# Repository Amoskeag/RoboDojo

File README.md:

# RoboDojo

This repo contains all the firmware and hardware for the RoboDojo.

If you're looking for the latest docs/builds, see our [Releases Page](https://github.com/Amoskeag/RoboDojo/releases).

# Getting Started

First, clone this repo (and optionally checkout a branch)

```shell
git clone --recurse-submodules https://github.com/Amoskeag/RoboDojo.git
cd RoboDojo
```

# Re-Init Submodules

Some libraries and resources are included as submodules, run the following
command to initialize them before opening the main sch

(If you get a missing library error, make sure to do this)

```shell
git submodule update --init --recursive
```

## Project Layout

If you want to use this project template for yourself, you can find it [here!](https://github.com/KenwoodFox/Project-Template)

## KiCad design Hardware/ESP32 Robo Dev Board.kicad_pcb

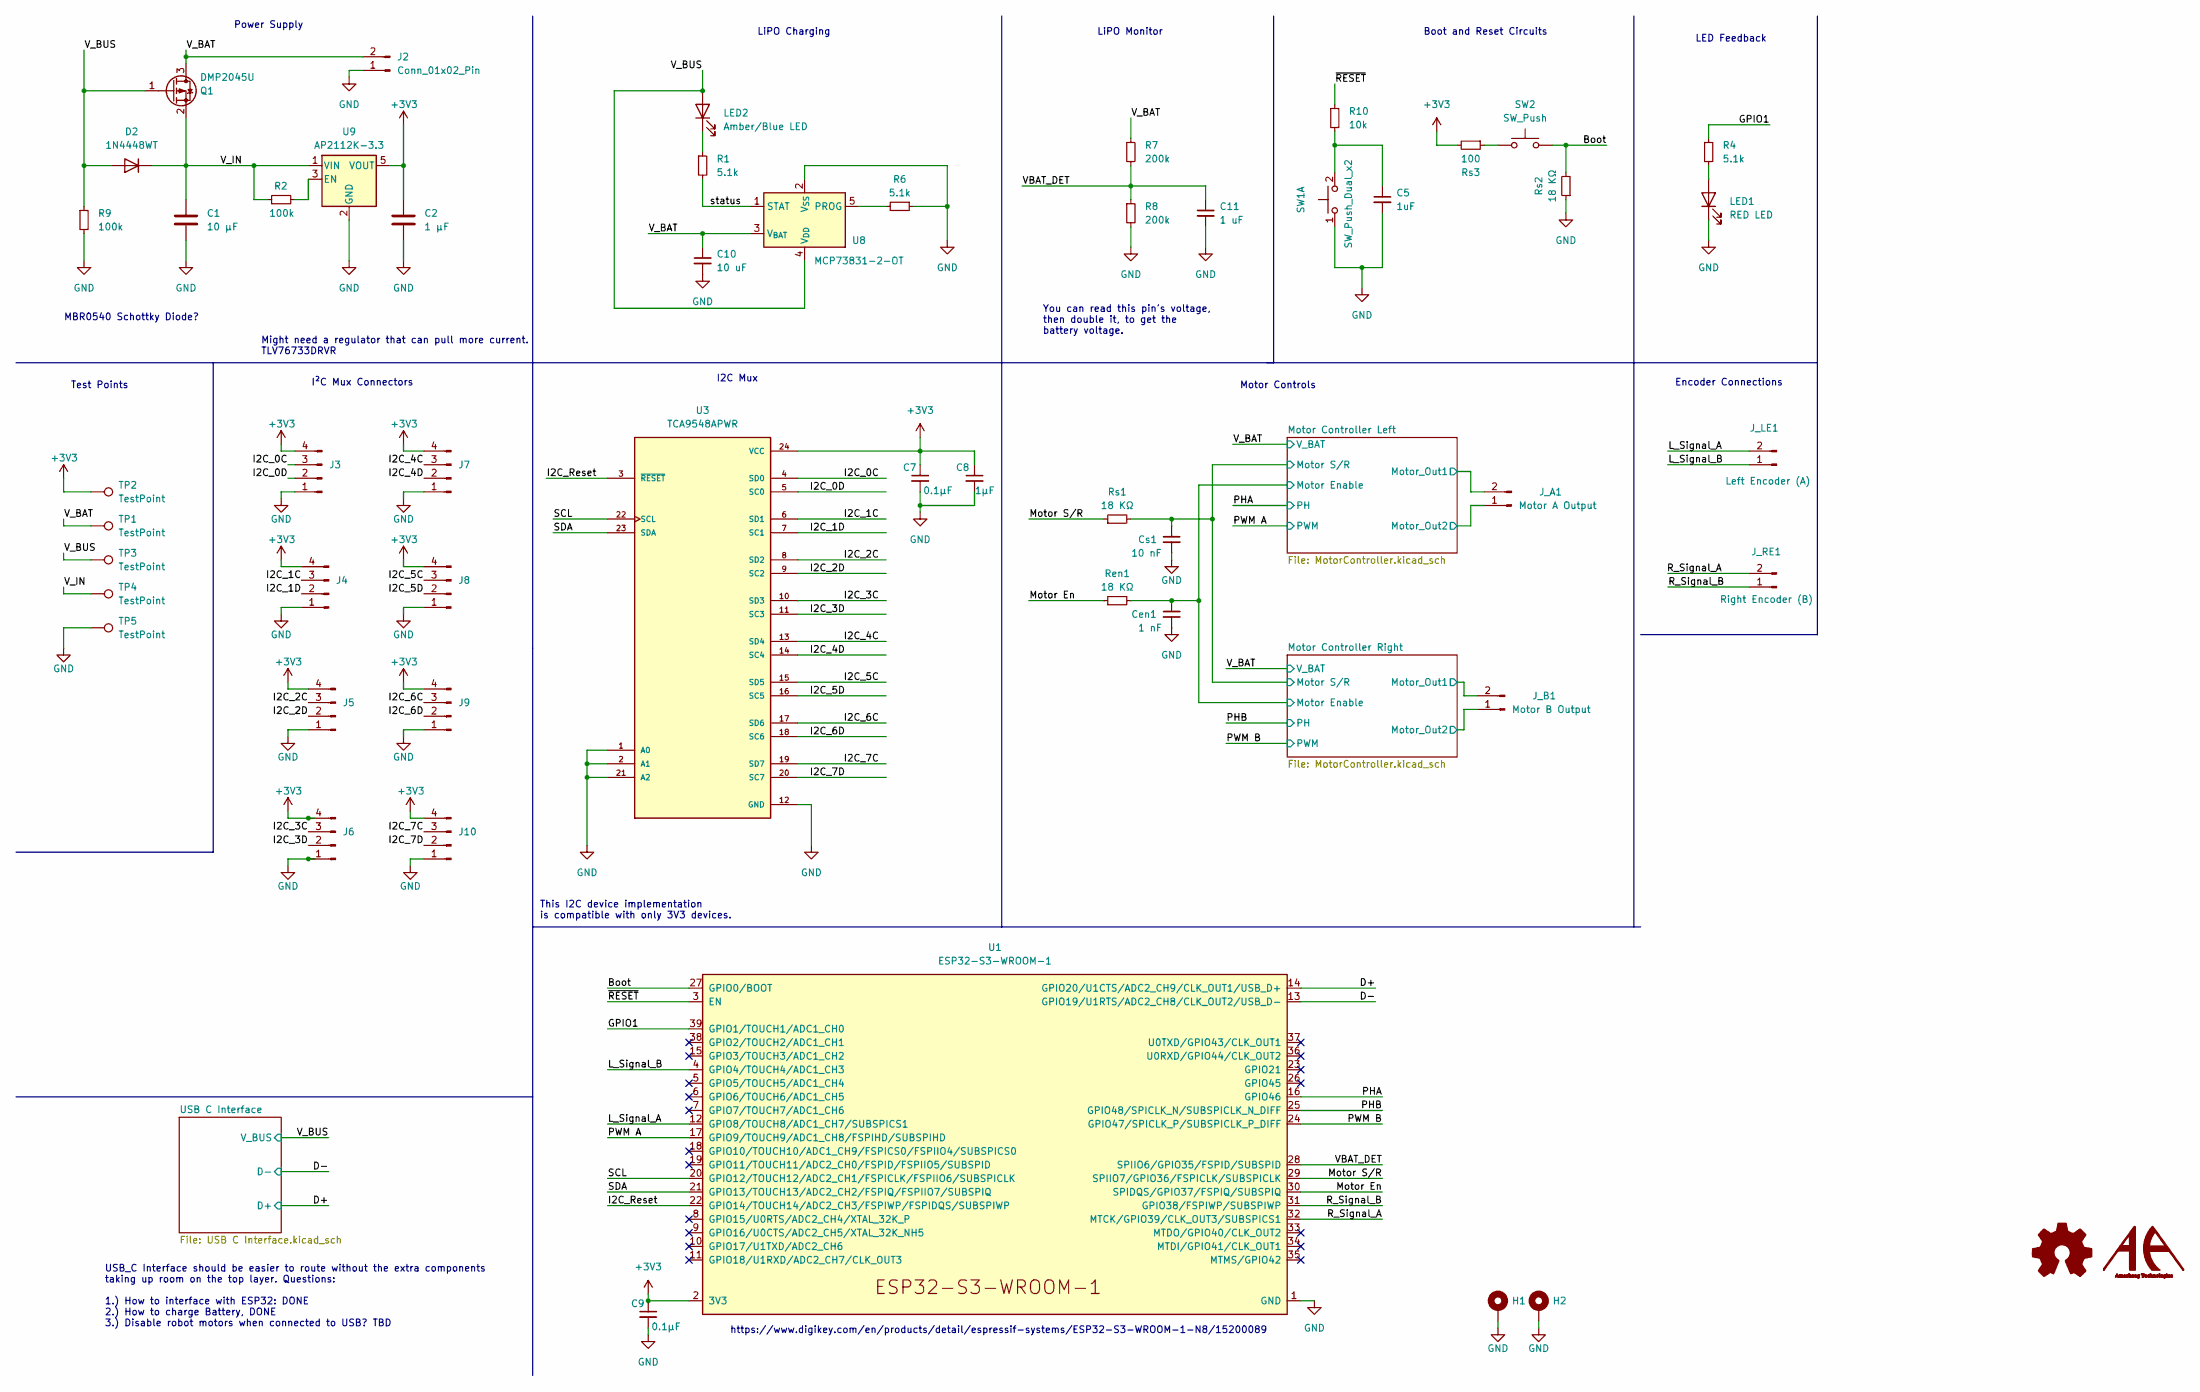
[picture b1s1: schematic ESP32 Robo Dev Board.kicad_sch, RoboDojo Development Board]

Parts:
C1: 10 µF; C_0805_2012Metric
C2: 1 µF; C_0805_2012Metric
C5: 1uF; C_0805_2012Metric
C7, C9: 0.1μF; C_0603_1608Metric
C8: 1μF; C_0603_1608Metric
C10: 10 uF; C_0805_2012Metric
C11: 1 uF; C_0805_2012Metric
Cen1: 1 nF; C_0603_1608Metric
Cs1: 10 nF; C_0603_1608Metric
D2: 1N4448WT; D_SOD-523
H1, H2: MountingHole_Pad; MountingHole_2.2mm_M2_DIN965_Pad
J2: Conn_01x02_Pin; JST_EH_B2B-EH-A_1x02_P2.50mm_Vertical
J3, J4, J5, J6, J7, J8, J9, J10: JST_SH_SM04B-SRSS-TB_1x04-1MP_P1.00mm_Horizontal
J_A1: Motor A Output; JST_EH_B2B-EH-A_1x02_P2.50mm_Vertical
J_B1: Motor B Output; JST_EH_B2B-EH-A_1x02_P2.50mm_Vertical
J_LE1: Left Encoder (A); JST_EH_B2B-EH-A_1x02_P2.50mm_Vertical
J_RE1: Right Encoder (B); JST_EH_B2B-EH-A_1x02_P2.50mm_Vertical
LED1: RED LED; LED_0805_2012Metric
LED2: Amber/Blue LED; LED_0805_2012Metric
Q1: DMP2045U; SOT-23
R1: 5.1k; R_0805_2012Metric
R2: 100k; R_0603_1608Metric
R4, R6: 5.1k; R_0603_1608Metric
R7, R8: 200k; R_0805_2012Metric
R9: 100k; R_0805_2012Metric
R10: 10k; R_0603_1608Metric
Ren1: 18 KΩ; R_0603_1608Metric
Rs1, Rs2: 18 KΩ; R_0603_1608Metric
Rs3: 100; R_0603_1608Metric
SW1: SW_Push_Dual_x2; SW_TH_Tactile_Omron_B3F-100x
SW2: SW_Push; SW_TH_Tactile_Omron_B3F-100x
TP1, TP2, TP3, TP4, TP5: TestPoint; TestPoint_Pad_D1.0mm
U1: ESP32-S3-WROOM-1
U3: TCA9548APWR; SOP65P640X120-24N; PARTREV G; DigiKey_Part_Number 296-34905-1-ND
U8: MCP73831-2-OT; SOT-23-5
U9: AP2112K-3.3; SOT-23-5

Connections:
+3V3: C2.1, C7.1, C8.1, C9.1, J3.4, J4.4, J5.4, J6.4, J7.4, J8.4, J9.4, J10.4, Rs3.2, TP2.1, U1.2 (3V3), U3.24 (VCC), U9.5 (VOUT)
/Boot: Rs2.2, SW2.2, U1.27 (GPIO0/BOOT)
/D+: U1.14 (GPIO20/U1CTS/ADC2_CH9/CLK_OUT1/USB_D+); also elsewhere on the board
/D-: U1.13 (GPIO19/U1RTS/ADC2_CH8/CLK_OUT2/USB_D-); also elsewhere on the board
/GPIO1: R4.1, U1.39 (GPIO1/TOUCH1/ADC1_CH0)
/I2C_0C: J3.3, U3.4 (SD0)
/I2C_0D: J3.2, U3.5 (SC0)
/I2C_1C: J4.3, U3.6 (SD1)
/I2C_1D: J4.2, U3.7 (SC1)
/I2C_2C: J5.3, U3.8 (SD2)
/I2C_2D: J5.2, U3.9 (SC2)
/I2C_3C: J6.3, U3.10 (SD3)
/I2C_3D: J6.2, U3.11 (SC3)
/I2C_4C: J7.3, U3.13 (SD4)
/I2C_4D: J7.2, U3.14 (SC4)
/I2C_5C: J8.3, U3.15 (SD5)
/I2C_5D: J8.2, U3.16 (SC5)
/I2C_6C: J9.3, U3.17 (SD6)
/I2C_6D: J9.2, U3.18 (SC6)
/I2C_7C: J10.3, U3.19 (SD7)
/I2C_7D: J10.2, U3.20 (SC7)
/I2C_Reset: U1.22 (GPIO14/TOUCH14/ADC2_CH3/FSPIWP/FSPIDQS/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), U3.3 (~RESET)
/L_Signal_A: J_LE1.2, U1.12 (GPIO8/TOUCH8/ADC1_CH7/SUBSPICS1)
/L_Signal_B: J_LE1.1, U1.4 (GPIO4/TOUCH4/ADC1_CH3)
/Motor Controller Left/EN/FAULT: Cen1.1, Ren1.2; also elsewhere on the board
/Motor Controller Left/Motor_Out1: J_A1.2; also elsewhere on the board
/Motor Controller Left/Motor_Out2: J_A1.1; also elsewhere on the board
/Motor Controller Left/STBY/RESET: Cs1.1, Rs1.2; also elsewhere on the board
/Motor Controller Right/Motor_Out1: J_B1.2; also elsewhere on the board
/Motor Controller Right/Motor_Out2: J_B1.1; also elsewhere on the board
/Motor En: Ren1.1, U1.30 (SPIDQS/GPIO37/FSPIQ/SUBSPIQ)
/Motor S/R: Rs1.1, U1.29 (SPIIO7/GPIO36/FSPICLK/SUBSPICLK)
/PHA: U1.16 (GPIO46); also elsewhere on the board
/PHB: U1.25 (GPIO48/SPICLK_N/SUBSPICLK_N_DIFF); also elsewhere on the board
/PWM A: U1.17 (GPIO9/TOUCH9/ADC1_CH8/FSPIHD/SUBSPIHD); also elsewhere on the board
/PWM B: U1.24 (GPIO47/SPICLK_P/SUBSPICLK_P_DIFF); also elsewhere on the board
/R_Signal_A: J_RE1.2, U1.32 (MTCK/GPIO39/CLK_OUT3/SUBSPICS1)
/R_Signal_B: J_RE1.1, U1.31 (GPIO38/FSPIWP/SUBSPIWP)
/SCL: U1.20 (GPIO12/TOUCH12/ADC2_CH1/FSPICLK/FSPIIO6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), U3.22 (SCL)
/SDA: U1.21 (GPIO13/TOUCH13/ADC2_CH2/FSPIQ/FSPIIO7/S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), U3.23 (SDA)
/VBAT_DET: C11.1, R7.2, R8.1, U1.28 (SPIIO6/GPIO35/FSPID/SUBSPID)
/V_BAT: C10.1, J2.2, Q1.3 (D), R7.1, TP1.1, U8.3 (V_{BAT}); also elsewhere on the board
/V_BUS: D2.2 (A), LED2.2 (A), Q1.1 (G), R9.1, TP3.1, U8.4 (V_{DD}); also elsewhere on the board
/V_IN: C1.1, D2.1 (K), Q1.2 (S), R2.1, TP4.1, U9.1 (VIN)
/status: R1.2, U8.1 (STAT)
/~RESET: R10.1, U1.3 (EN)
GND: C1.2, C2.2, C5.2, C7.2, C8.2, C9.2, C10.2, C11.2, Cen1.2, Cs1.2, H1.1, H2.1, J2.1, J3.1, J4.1, J5.1, J6.1, J7.1, J8.1, J9.1, J10.1, LED1.1 (K), R6.1, R8.2, R9.2, Rs2.1, SW1.1 (C), TP5.1, U1.1 (GND), U1.40 (GND), U1.41 (GND), U3.1 (A0), U3.2 (A1), U3.12 (GND), U3.21 (A2), U8.2 (V_{SS}), U9.2 (GND); also elsewhere on the board
unnamed: LED1.2 (A), R4.2
unnamed: LED2.1 (K), R1.1
unnamed: Rs3.1, SW2.1
unnamed: C5.1, R10.2, SW1.2 (D)
unnamed: R6.2, U8.5 (PROG)
unnamed: R2.2, U9.3 (EN)

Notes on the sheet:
USB_C Interface should be easier to route without the extra components taking up room on the top layer. Questions: 1.) How to interface with ESP32: DONE 2.) How to charge Battery, DONE 3.) Disable robot motors when connected to USB? TBD
LiPO Monitor
MBR0540 Schottky Diode?
https://www.digikey.com/en/products/detail/espressif-systems/ESP32-S3-WROOM-1-N8/15200089
Motor Controls
Encoder Connections
Boot and Reset Circuits
This I2C device implementation is compatible with only 3V3 devices.
You can read this pin's voltage, then double it, to get the battery voltage.
LED Feedback
I²C Mux Connectors
I2C Mux
Test Points
Power Supply
LiPO Charging
Might need a regulator that can pull more current. TLV76733DRVR

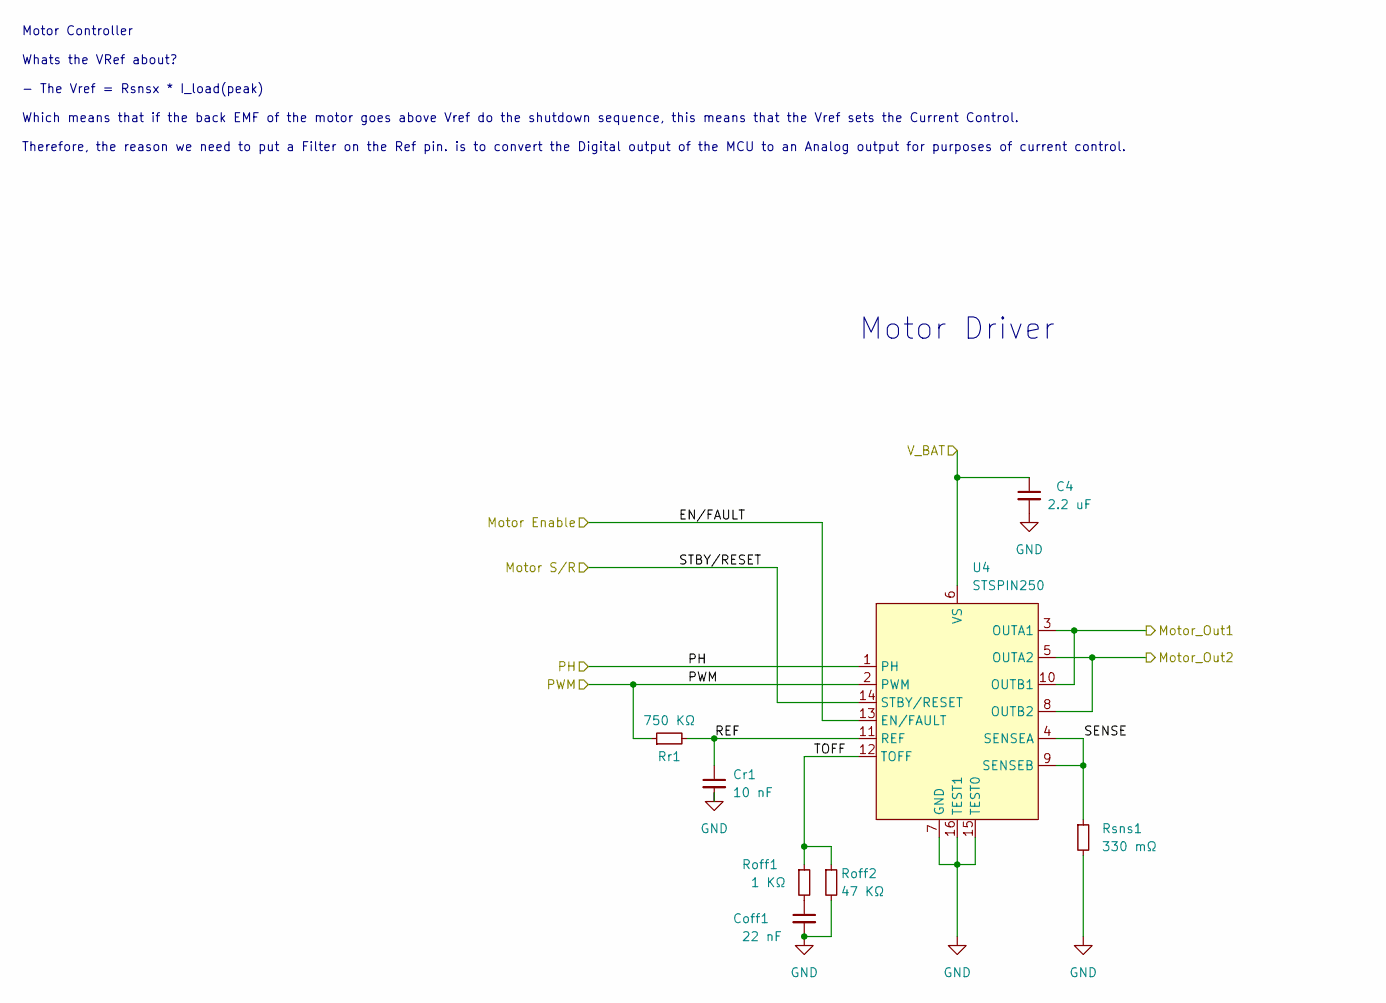
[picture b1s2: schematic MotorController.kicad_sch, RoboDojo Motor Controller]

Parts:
C4: 2.2 uF; C_0603_1608Metric
Coff1: 22 nF; C_0603_1608Metric
Cr1: 10 nF; C_0603_1608Metric
Roff1: 1 KΩ; R_0603_1608Metric
Roff2: 47 KΩ; R_0603_1608Metric
Rr1: 750 KΩ; R_0603_1608Metric
Rsns1: 330 mΩ; R_0805_2012Metric
U4: STSPIN250; ST_Microelectronics-STSPIN250-0

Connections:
/Motor Controller Left/EN/FAULT: U4.13 (EN/FAULT); also elsewhere on the board
/Motor Controller Left/Motor_Out1: U4.3 (OUTA1), U4.10 (OUTB1); also elsewhere on the board
/Motor Controller Left/Motor_Out2: U4.5 (OUTA2), U4.8 (OUTB2); also elsewhere on the board
/Motor Controller Left/REF: Cr1.1, Rr1.2, U4.11 (REF)
/Motor Controller Left/SENSE: Rsns1.1, U4.4 (SENSEA), U4.9 (SENSEB)
/Motor Controller Left/STBY/RESET: U4.14 (STBY/RESET); also elsewhere on the board
/Motor Controller Left/TOFF: Roff1.1, Roff2.1, U4.12 (TOFF)
/PHA: U4.1 (PH); also elsewhere on the board
/PWM A: Rr1.1, U4.2 (PWM); also elsewhere on the board
/V_BAT: C4.1, U4.6 (VS); also elsewhere on the board
GND: C4.2, Coff1.2, Cr1.2, Roff2.2, Rsns1.2, U4.7 (GND), U4.15 (TEST0), U4.16 (TEST1); also elsewhere on the board
unnamed: Coff1.1, Roff1.2

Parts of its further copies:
C6: 2.2 uF; C_0603_1608Metric
Coff2: 22 nF; C_0603_1608Metric
Cr2: 10 nF; C_0603_1608Metric
Roff3: 1 KΩ; R_0603_1608Metric
Roff4: 47 KΩ; R_0603_1608Metric
Rr2: 750 KΩ; R_0603_1608Metric
Rsns2: 330 mΩ; R_0805_2012Metric
U5: STSPIN250; ST_Microelectronics-STSPIN250-0

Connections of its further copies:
/Motor Controller Left/EN/FAULT: U5.13 (EN/FAULT); also elsewhere on the board
/Motor Controller Left/STBY/RESET: U5.14 (STBY/RESET); also elsewhere on the board
/Motor Controller Right/Motor_Out1: U5.3 (OUTA1), U5.10 (OUTB1); also elsewhere on the board
/Motor Controller Right/Motor_Out2: U5.5 (OUTA2), U5.8 (OUTB2); also elsewhere on the board
/Motor Controller Right/REF: Cr2.1, Rr2.2, U5.11 (REF)
/Motor Controller Right/SENSE: Rsns2.1, U5.4 (SENSEA), U5.9 (SENSEB)
/Motor Controller Right/TOFF: Roff3.1, Roff4.1, U5.12 (TOFF)
/PHB: U5.1 (PH); also elsewhere on the board
/PWM B: Rr2.1, U5.2 (PWM); also elsewhere on the board
/V_BAT: C6.1, U5.6 (VS); also elsewhere on the board
GND: C6.2, Coff2.2, Cr2.2, Roff4.2, Rsns2.2, U5.7 (GND), U5.15 (TEST0), U5.16 (TEST1); also elsewhere on the board
unnamed: Coff2.1, Roff3.2

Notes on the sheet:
Motor Driver
Motor Controller Whats the VRef about? - The Vref = Rsnsx * I_load(peak) Which means that if the back EMF of the motor goes above Vref do the shutdown sequence, this means that the Vref sets the Current Control. Therefore, the reason we need to put a Filter on the Ref pin. is to convert the Digital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

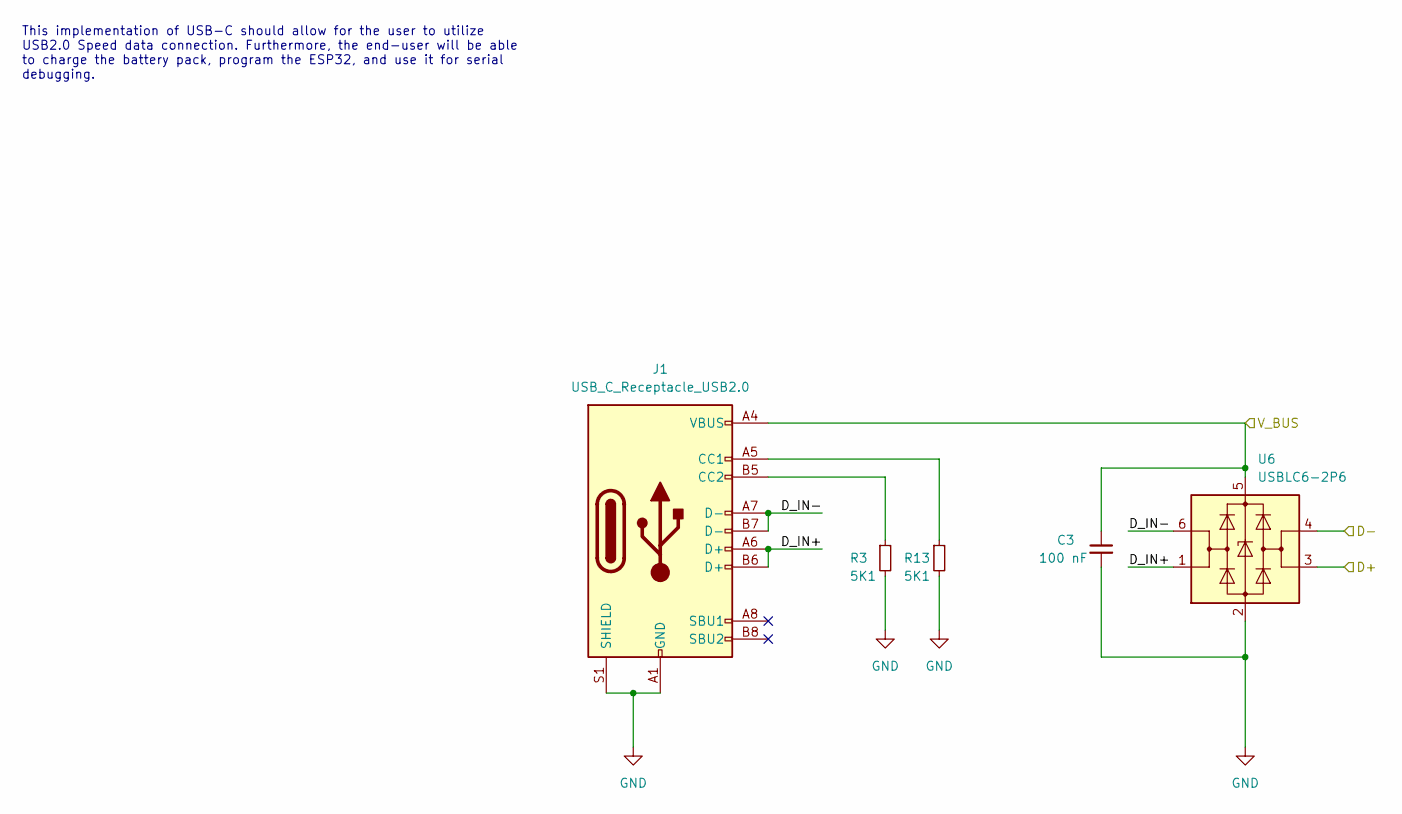
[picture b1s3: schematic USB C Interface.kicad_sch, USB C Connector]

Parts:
C3: 100 nF; C_0603_1608Metric
J1: USB_C_Receptacle_USB2.0; GCT_USB4110GFA
R3, R13: 5K1; R_0603_1608Metric
U6: USBLC6-2P6; SOT-666

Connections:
/D+: U6.3 (I/O2); also elsewhere on the board
/D-: U6.4 (I/O2); also elsewhere on the board
/USB C Interface/D_IN+: J1.A6 (D+), J1.B6 (D+), U6.1 (I/O1)
/USB C Interface/D_IN-: J1.A7 (D-), J1.B7 (D-), U6.6 (I/O1)
/V_BUS: C3.1, J1.A4 (VBUS), J1.A9 (VBUS), J1.B4 (VBUS), J1.B9 (VBUS), U6.5 (VBUS); also elsewhere on the board
GND: C3.2, J1.A1 (GND), J1.A12 (GND), J1.B1 (GND), J1.B12 (GND), J1.S1 (SHIELD), R3.2, R13.2, U6.2 (GND); also elsewhere on the board
unnamed: J1.A5 (CC1), R13.1
unnamed: J1.B5 (CC2), R3.1

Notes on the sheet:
This implementation of USB-C should allow for the user to utilize USB2.0 Speed data connection. Furthermore, the end-user will be able to charge the battery pack, program the ESP32, and use it for serial debugging.

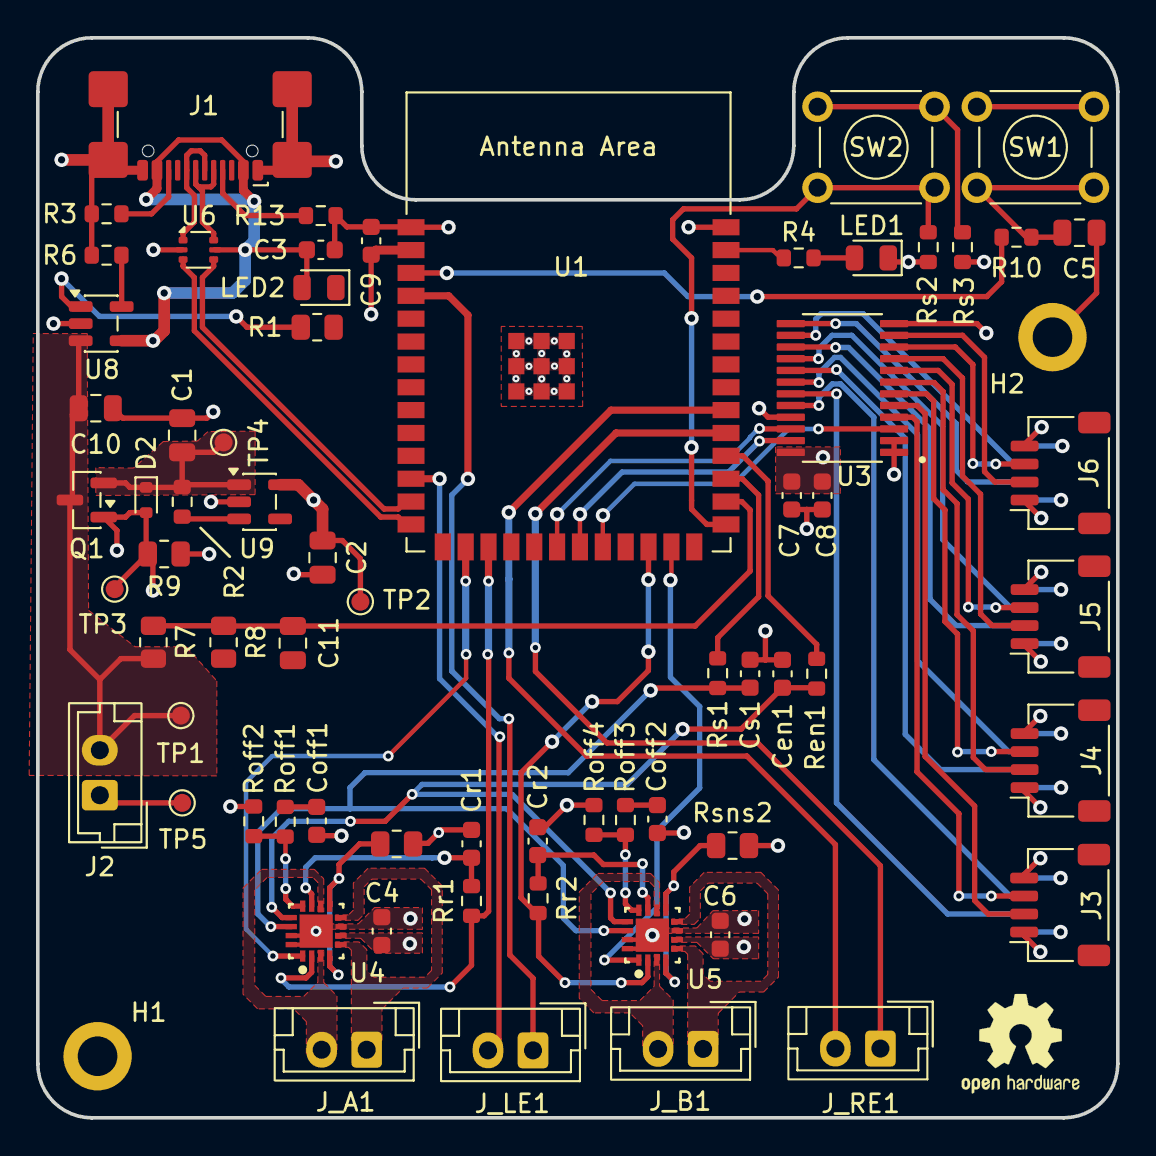
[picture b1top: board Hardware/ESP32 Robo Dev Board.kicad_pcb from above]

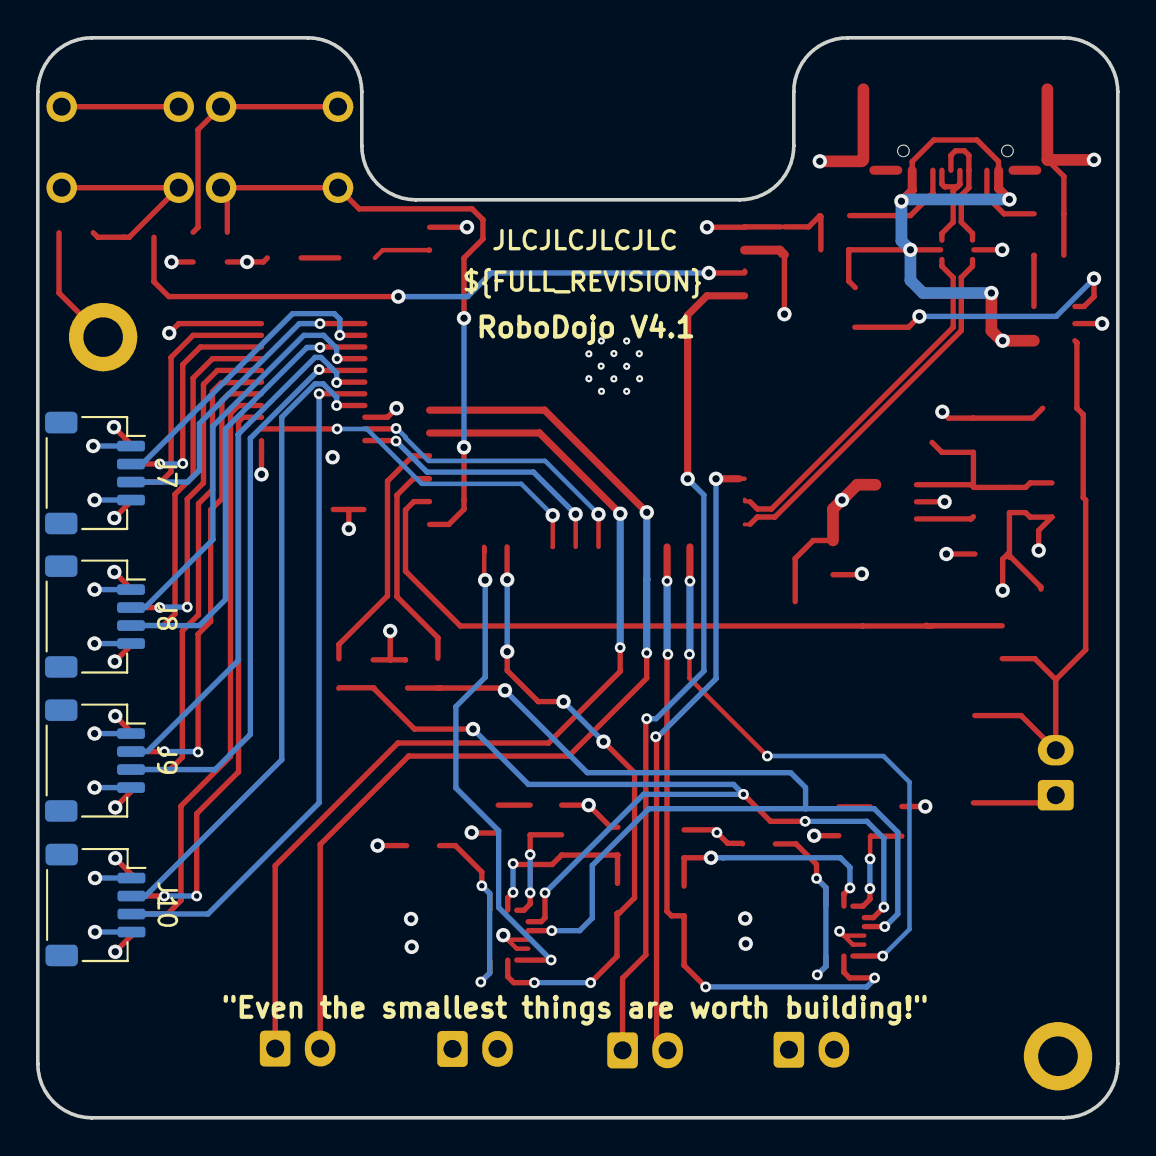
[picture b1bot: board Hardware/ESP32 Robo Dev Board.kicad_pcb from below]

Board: 4 copper layers, 60.0 x 60.0 mm, 73 parts (4 on the bottom side), 65 nets.

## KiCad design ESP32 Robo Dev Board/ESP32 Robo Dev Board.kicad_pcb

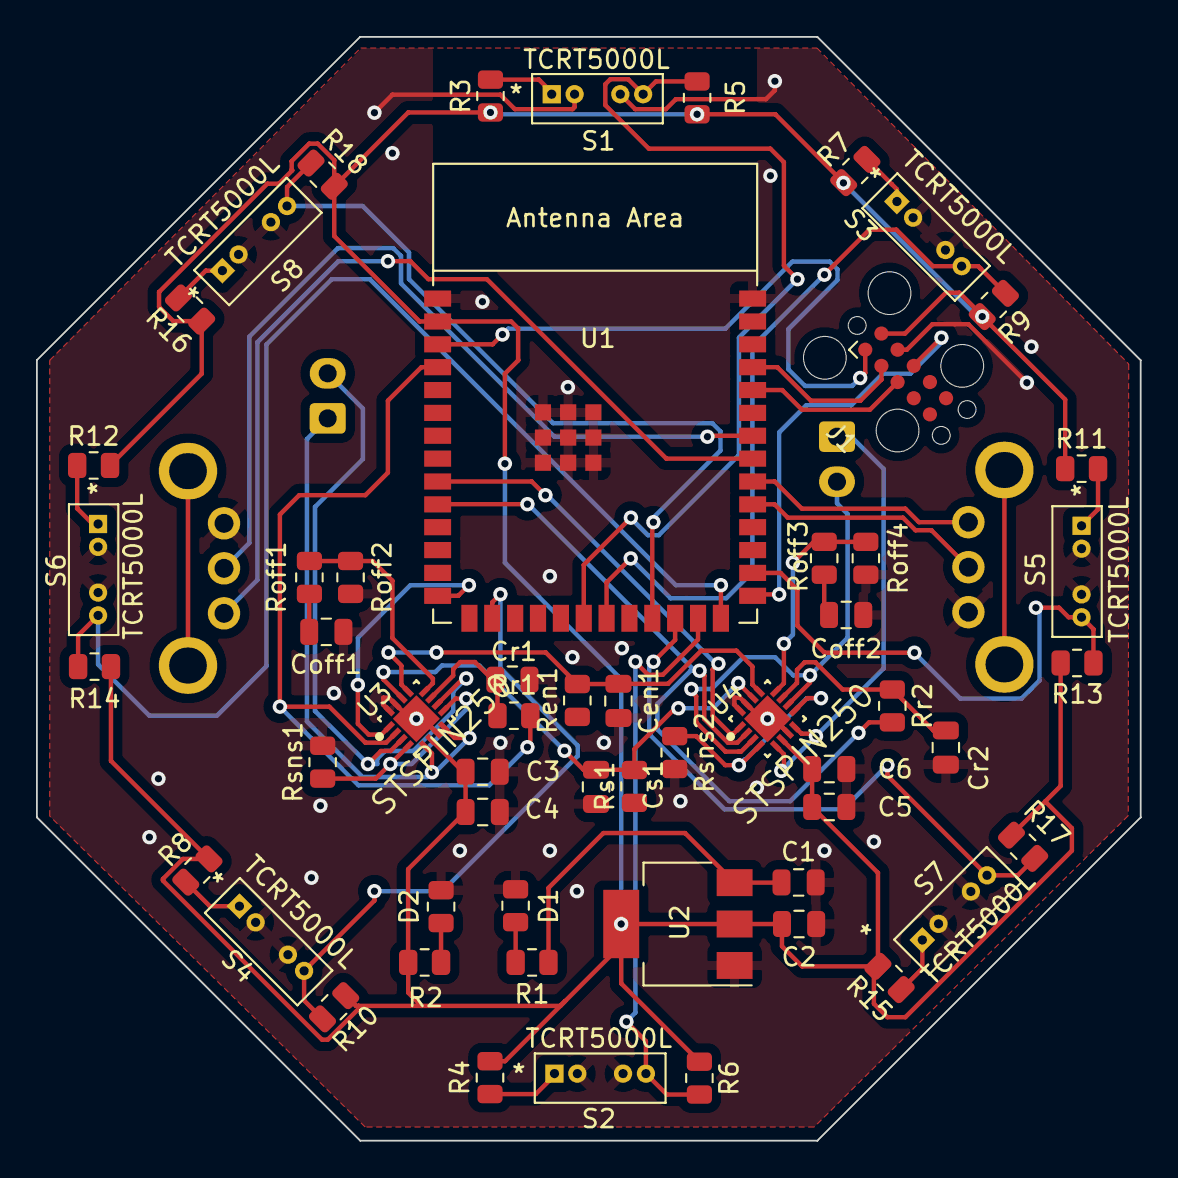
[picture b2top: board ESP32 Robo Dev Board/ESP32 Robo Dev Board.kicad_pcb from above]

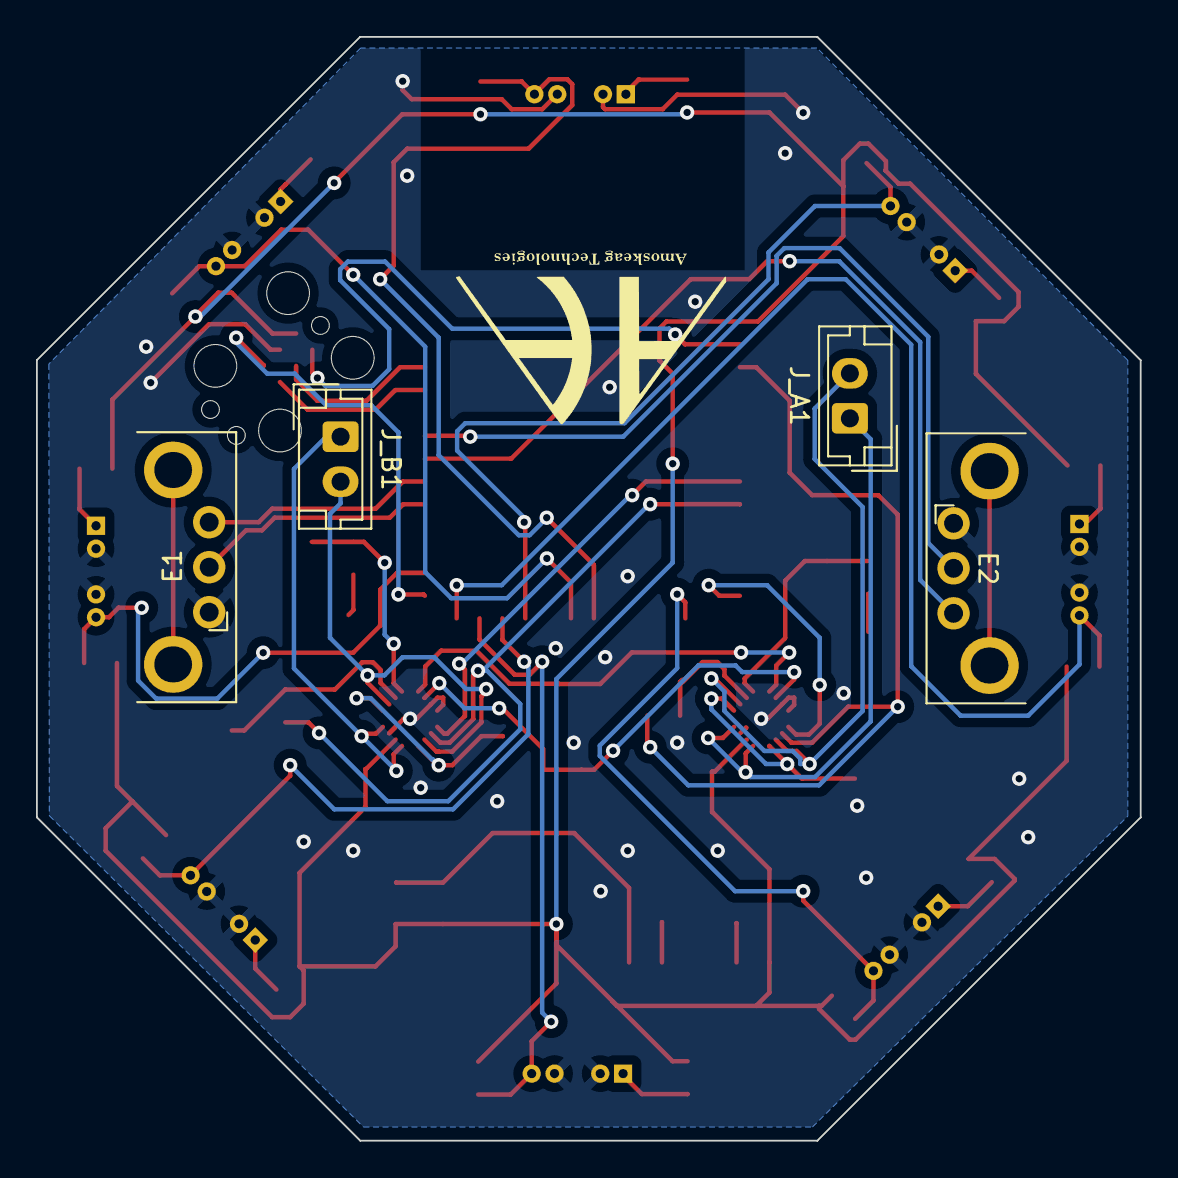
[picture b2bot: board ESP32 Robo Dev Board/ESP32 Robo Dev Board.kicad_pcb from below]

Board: 2 copper layers, 61.3 x 61.3 mm, 59 parts (4 on the bottom side), 47 nets.

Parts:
C1, C2: 2.2 µF; C_0805_2012Metric
C3, C5: 22 uF; C_0805_2012Metric
C4, C6: 2.2 uF; C_0805_2012Metric
Cen1: 1 nF; C_0805_2012Metric
Coff1, Coff2: 22 nF; C_0805_2012Metric
Cr1, Cr2: 10000 pF; C_0805_2012Metric
Cs1: 10 nF; C_0805_2012Metric
D1, D2: LED; R_0805_2012Metric
E1: Encoder_L; Kailh Encoder 9mm
E2: Encoder_R; Kailh Encoder 9mm
J1: PRG; Tag-Connect_TC2050-IDC-FP_2x05_P1.27mm_Vertical
J_A1: Motor A Output; JST_EH_B2B-EH-A_1x02_P2.50mm_Vertical
J_B1: Motor B Output; JST_EH_B2B-EH-A_1x02_P2.50mm_Vertical
R1, R2: 2K; R_0805_2012Metric
R3, R4, R7, R8, R11, R12, R15, R16: 550R; R_0805_2012Metric
R5, R6, R9, R10, R13, R14, R17, R18: 1.5K; R_0805_2012Metric
Ren1: 18 KΩ; R_0805_2012Metric
Roff1, Roff3: 1 KΩ; R_0805_2012Metric
Roff2, Roff4: 47 KΩ; R_0805_2012Metric
Rr1, Rr2: 750 KΩ; R_0805_2012Metric
Rs1: 18 KΩ; R_0805_2012Metric
Rsns1, Rsns2: 330 mΩ; R_0805_2012Metric
S1, S2, S3, S4, S5, S6, S7, S8: TCRT5000L
U1: ESP32-S3-WROOM-1
U2: AMS1117-3.3; SOT-223-3_TabPin2
U3, U4: STSPIN250; ST_Microelectronics-STSPIN250-0

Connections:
+3V3: C2.1, C3.2, C4.1, C5.2, C6.1, J1.10, R2.2, R3.1, R4.1, R5.1, R6.1, R7.1, R8.1, R9.1, R10.1, R11.1, R12.1, R13.1, R14.1, R15.1, R16.1, R17.1, R18.1, U1.2 (3V3), U2.2 (VO), U3.6 (VS), U4.6 (VS)
+5V: C1.1, R1.2, U2.3 (VI)
/Boot: J1.8, U1.27 (GPIO0/BOOT)
/Enable: J1.1, U1.3 (EN)
/IR1: R5.2, S1.4 (C), U1.20 (GPIO12/TOUCH12/ADC2_CH1/FSPICLK/FSPIIO6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)
/IR2: R9.2, S3.4 (C), U1.21 (GPIO13/TOUCH13/ADC2_CH2/FSPIQ/FSPIIO7/S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)
/IR3: R13.2, S5.4 (C), U1.28 (SPIIO6/GPIO35/FSPID/SUBSPID)
/IR4: R17.2, S7.4 (C), U1.24 (GPIO47/SPICLK_P/SUBSPICLK_P_DIFF)
/IR5: R6.2, S2.4 (C), U1.25 (GPIO48/SPICLK_N/SUBSPICLK_N_DIFF)
/IR6: R10.2, S4.4 (C), U1.16 (GPIO46)
/IR7: R14.2, S6.4 (C), U1.26 (GPIO45)
/IR8: R18.2, S8.4 (C), U1.23 (GPIO21)
/L_Signal_A: E1.2 (A), U1.31 (GPIO38/FSPIWP/SUBSPIWP)
/L_Signal_B: E1.3 (B), U1.32 (MTCK/GPIO39/CLK_OUT3/SUBSPICS1)
/Motor Controller Left/Motor Enable: Cen1.1, Ren1.2, U3.13 (EN/FAULT), U4.13 (EN/FAULT)
/Motor Controller Left/Motor S/R: Cs1.1, Rs1.2, U3.14 (STBY/RESET), U4.14 (STBY/RESET)
/Motor Controller Left/Motor_Out1: J_A1.2, U3.3 (OUTA1), U3.10 (OUTB1)
/Motor Controller Left/Motor_Out2: J_A1.1, U3.5 (OUTA2), U3.8 (OUTB2)
/Motor Controller Right/Motor_Out1: J_B1.2, U4.3 (OUTA1), U4.10 (OUTB1)
/Motor Controller Right/Motor_Out2: J_B1.1, U4.5 (OUTA2), U4.8 (OUTB2)
/PHA: U1.14 (GPIO20/U1CTS/ADC2_CH9/CLK_OUT1/USB_D+), U3.1 (PH)
/PHB: U1.9 (GPIO16/U0CTS/ADC2_CH5/XTAL_32K_NH5), U4.1 (PH)
/PWM A: Rr1.1, U1.4 (GPIO4/TOUCH4/ADC1_CH3), U3.2 (PWM)
/PWM B: Rr2.1, U1.10 (GPIO17/U1TXD/ADC2_CH6), U4.2 (PWM)
/R_Signal_A: E2.2 (A), U1.34 (MTDI/GPIO41/CLK_OUT1)
/R_Signal_B: E2.3 (B), U1.33 (MTDO/GPIO40/CLK_OUT2)
/Rx: J1.3, U1.36 (U0RXD/GPIO44/CLK_OUT2)
/Tx: J1.2, U1.37 (U0TXD/GPIO43/CLK_OUT1)
GND: C1.2, C2.2, C3.1, C4.2, C5.1, C6.2, Cen1.2, Coff1.2, Coff2.2, Cr1.2, Cr2.2, Cs1.2, D1.1 (K), D2.1 (K), E1.1 (COM), E2.1 (COM), J1.9, Roff2.2, Roff4.2, Rsns1.2, Rsns2.2, S1.2 (LED-), S1.3 (E), S2.2 (LED-), S2.3 (E), S3.2 (LED-), S3.3 (E), S4.2 (LED-), S4.3 (E), S5.2 (LED-), S5.3 (E), S6.2 (LED-), S6.3 (E), S7.2 (LED-), S7.3 (E), S8.2 (LED-), S8.3 (E), U1.1 (GND), U1.40 (GND), U1.41 (GND), U2.1 (GND), U3.7 (GND), U3.15 (TEST0), U3.16 (TEST1), U4.7 (GND), U4.15 (TEST0), U4.16 (TEST1)
unnamed: Coff1.1, Roff1.2
unnamed: Coff2.1, Roff3.2
unnamed: Cr1.1, Rr1.2, U3.11 (REF)
unnamed: Cr2.1, Rr2.2, U4.11 (REF)
unnamed: D1.2 (A), R1.1
unnamed: D2.2 (A), R2.1
unnamed: R3.2, S1.1 (LED+)
unnamed: R4.2, S2.1 (LED+)
unnamed: R7.2, S3.1 (LED+)
unnamed: R8.2, S4.1 (LED+)
unnamed: R11.2, S5.1 (LED+)
unnamed: R12.2, S6.1 (LED+)
unnamed: R15.2, S7.1 (LED+)
unnamed: R16.2, S8.1 (LED+)
unnamed: Roff1.1, Roff2.1, U3.12 (TOFF)
unnamed: Roff3.1, Roff4.1, U4.12 (TOFF)
unnamed: Rsns1.1, U3.4 (SENSEA), U3.9 (SENSEB)
unnamed: Rsns2.1, U4.4 (SENSEA), U4.9 (SENSEB)

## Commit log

2022-11-30 Remove some mess and include new .gitignore
2022-11-30 Create simple readme
2022-12-01 First Finished Version 0.1.
2022-12-01 Bump amoskeag custom library
2022-12-01 Add battery connector
2022-12-01 Use robots
2022-12-01 More robots (and cleanups)
2022-12-01 Fixup! Better anotations
2022-12-01 Include copy of espressifs library
2022-12-01 Fixup! Typos
2022-12-01 Fixup fixups
2022-12-02 Fix Range Finder Locations
2022-12-02 Add license Fix typo in hardware workflow:
2022-12-04 Rebuild Layout
    Took the V1.0 Layout and reworked it.
2022-12-05 Update ESP32 Robo Dev Board.kicad_pcb
    Update Silkscreen, Move Components to better fit silkscreen
2022-12-10 Add I2C IC
    Added TCA9548A mux interface
2023-01-27 Update ESP32 Robo Dev Board.kicad_pcb
    Add in TCA9548A Multiplexer.
    Reroute traces.
    Prepare for Proximity Sensor overhaul
2023-01-29 Add new array for sensors
    Add in sensor array
    Begin trace reroute
2023-01-29 Fix 3d and placement
2023-01-29 I2C Interface Established
    Run Traces for all Sensors
    Mark unused Pins
    Sub-Optimally run said traces
2023-01-30 Fix DRC errors
    Fix DRC errors, move sensor array closer to center
2023-01-30 Upkeep
    Add GND to mounts
    Move traces from antenna
2023-01-30 Fix Thoughholes
    Fixed Schematic Parity DRC issue.
    Taught some standard practices by the Foxy Boy
2023-01-30 Add Throughholes
    Added Through holes in a far better what than before.
    Got advice from the Foxy Fellow
2023-03-28 Fix Traces
    trace fixes
2023-03-28 Attempt to recover pcb
2023-04-06 Update, Fix DRC Errors after The Great Recovery
    Traces got messed up, fixed and tried to establish a keep out zone for the Antena.
2023-08-18 Fixed Traces
    Fix Traces that I messed up when I left college. Getting back to the project.
2023-08-18 Add USB C in Schematic
    Added USB C support in sch not on PCB yet
2023-09-06 Add VL53L0X
    Added VL53L0X range finders and reworked traces.
2023-11-26 Everything Changes
    Lets Fix it.
2023-11-28 Fix Reroute
    Traces are getting messy, Moved the TOF sensors to be 3mm from edge of board. USB-C getting moved possibly. Changed Resistor and Capacitor footprints to better fit board space requirements.
2023-11-28 Update, all passive components.
    Placed all parts, time to route.
2023-11-29 Update Trace Routing
    Lots of DRC errors related to mismatching Library entries. Thermal Relief Parameters need to be checked. USB-C Remains a swept under the rug feature.
2023-11-30 add kicad7 footprint fp lib table
2023-11-30 Update Amoskeag_KiCAD_Libs
2023-11-30 Import from https://github.com/KenwoodFox/Project-Template
2023-11-30 Remove USB-C
    USB C needs 4 layer for this. Remove now, profit later.
2023-11-30 Removed USB C
    rerouted traces
2023-11-30 Fix path
2023-11-30 Move Traces for Cleanup
    Cleanup for Version 3 Release
2023-12-06 Small update, traces
    Increase spacing between traces on left side
2024-01-09 Create 4-Layer Update
    Lay foundation for 4-Layer PCB Update
2024-03-04 BIG Changes
    Create a 4 Layer Variation
    Change Motor Controller routing.
    Change Power Regulation.
    Optimize Sensor routing.
    Pray I know what i'm doing
2024-03-05 Updated Motor Driver Routing
    Working on Power Supply and Motor Controller Routing
2025-01-15 4 L:ayer Board with USB-C
    Created a 4-Layer PCB with USB-C updates
2025-10-04 Square Board Time
    Rerouting, restarting project, trying to make a simpler dev board. Lets see what we can do.
2025-10-04 update 2025
    board refactor
2025-10-05 Board Refactor, Updated Parts
    Updated Board layout and added new parts
2025-10-05 Update I2C Bus Connections
    Channel 4 of I2C was not connected, will make traces pretty later.
2025-10-05 Tweaked n' fixed things with @Amoskeag
2025-10-09 Squashed commit of the following:
    commit e6d18f1838a18780ff985c290e2821e2ac438ddc
    Author: KenwoodFox <kenwood364@gmail.com>
    Date: Sun Oct 5 18:23:23 2025 -0400
    Tweaked n' fixed things with @Amoskeag
    commit 133f082a76a13551d058af83ac953c852f82cbfb
    Author: Arthur Aznive <61330561+Amoskeag@users.noreply.github.com>
2025-10-09 Updating Workflow yml file
    Updated the versions that are being targeted.
2025-10-09 Updated hardware_workflow.yml
    Updated the KiBot Target to k9!
2025-10-12 Fix Footprint Targets
    Fixed DRC errors on footprints.
2025-10-13 Add JST Connectors for Encoders
    Added JST Connectors for my Encoders to attach to.
    Fixed all DRC Errors.
2025-10-16 Increase Trace Widths
    Increased the smallest trace width from 0.25 mm to 0.3 mm and beefed up all the other traces.
2025-10-19 Clean Up Schematic
    Fixed Schematic notes, and formatting
2025-10-19 Fix Bad 3D Model Path
    USB-C Connector Model was not being rendered, fixed path issue.
2026-02-16 Fix DRC Errors
    Silkscreen overlapping and some trace width modification.
2026-02-16 Update Layer Names
    Looks like changing layer names makes JLC not recognize layers, changed back to default settings for naming.
2026-03-11 Standardize I²C Bus and Route USB-C
    Taking the opportunity to reroute and place STEMMA QT (JST-SH) Connectors to standardize the use of the I²C Multiplexer. Also took the chance to clean up the USB-C power supply and data line routing.
2026-03-11 Fix DRC Errors
    Fixed small DRC errors.

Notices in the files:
parts and their libraries:
Copyright 2021 Accelerated Designs. All rights reserved.
